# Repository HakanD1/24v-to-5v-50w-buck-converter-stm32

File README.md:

# STM32 Digitally Controlled 24V to 5V (50W) Buck Converter

A high-performance, fully custom **closed-loop digitally controlled buck converter** capable of stepping down a 24V DC input to a highly stable 5V DC output, providing up to 10A (50W) of continuous power. 

This project integrates custom PCB hardware, STM32 embedded software, mathematical control algorithms, and a Nextion HMI (Human-Machine Interface) into a single, cohesive industrial-grade prototype.
> ⚠️ **Project Status:** Rather than turning this into a physical product, I built it as an R&D exercise to combine the full design, simulation, and firmware development process into a single project and put my theoretical background into practice. As a result, the PCB, schematic, and firmware files in this repo have not been manufactured — they've only been verified through design and simulation.

## 🌟 Key Features

*   **Robust Power Delivery:** 24V to 5V step-down conversion with up to 10A current capacity.
*   **Digital PI Control:** Real-time Proportional-Integral (PI) control loop running on an STM32 microcontroller to dynamically adjust the 120 kHz PWM duty cycle for perfect voltage/current regulation.
*   **Precision Measurement:** Hall-effect current sensing (ACS712) and voltage divider networks, both buffered by MCP6001 Op-Amps for noise-immune ADC readings via DMA.
*   **Advanced Gate Driving:** FAN73711 high-speed gate driver implemented to efficiently switch the N-Channel power MOSFET with minimal switching losses.
*   **Multi-Stage Auxiliary Power:** Dual XL4015 buck stages (24V→12V, 12V→5V) and an AMS1117-3.3V LDO to safely isolate and power the logic and driver circuits.
*   **Comprehensive Protection:** Input fuse, varistor for overvoltage spikes, inrush current-limiting thermistor, and a software-controlled mechanical relay for emergency cutoff.
*   **Interactive UI:** Nextion display integration via USART for real-time monitoring (V, I, P) and on-the-fly PI tuning, calibration, and mode switching.

## 🛠️ Hardware Architecture

The custom dual-layer PCB is designed with best practices in mind, separating noisy power switching nodes from sensitive analog measuring circuits.

*   **Power Stage:** Features a 33µH power inductor and low-ESR capacitors optimized through MATLAB/Simulink and LTspice simulations to minimize output ripple.
*   **Protection Layer:** Hardware-level protection blocks ensuring safe start-up and transient spike absorption.
*   **Connectivity:** Features industry-standard ports including USB Type-C (for communication/future updates), 4-pin SWD (for flashing/debugging), and a 4-pin USART header for the HMI.

## 💻 Software & Control Strategy

Developed using **STM32CubeIDE** and the HAL library, the software architecture operates in a non-blocking, interrupt-driven manner:

1.  **ADC via DMA:** Voltage and current analog signals are continuously sampled in the background.
2.  **Calibration Layer:** Raw ADC data is scaled using dynamically adjustable calibration multipliers (`V_Cal`, `I_Cal`) and offsets to compensate for real-world component tolerances.
3.  **PI Algorithm:** Compares the measured value against the user-defined reference. The accumulated error (Integral) and current error (Proportional) dynamically update the timer's compare register to adjust the 120 kHz PWM duty cycle.
4.  **UART Parser:** A custom interrupt-driven parser processes commands from the Nextion screen (e.g., `KPV:2.50`, `SETV:5.00`) to tune the system on the fly.

## 📂 Repository Structure

*   `/bom` - Bill of Materials (BOM) files.
*   `/cubemx` - STM32CubeIDE project workspace and C/C++ source code.
*   `/gerber` - PCB manufacturing and Gerber files.
*   `/Nextion` - Nextion HMI display interface and GUI files.
*   `/schematic_pcb_3d` & `/STEP file` - 3D models and CAD files of the PCB.
*   `buck converter V6.*` - KiCad schematic and PCB design files.
*   `Buck_converter_24Vto5V.asc` - LTspice simulation model.
*   `buck_converter_24Vto5V.slx` - MATLAB/Simulink model.
*   `REPORT.pdf` - Comprehensive project documentation and theoretical calculations (in Turkish).

## 🚀 Getting Started

1.  Clone this repository: `git clone https://github.com/HakanD1/24v-to-5v-50w-buck-converter-stm32`
2.  Open the `/cubemx` project folder in **STM32CubeIDE**.
3.  Compile and flash the firmware onto the STM32F103C8T6 via the SWD interface.
4.  Load the `.tft` file (located in the `/Nextion` folder) onto your Nextion display.
5.  Supply 24V to the main input terminal, and monitor the live parameters on the Nextion screen.

## 📄 License

This project is licensed under the MIT License - see the [LICENSE](LICENSE) file for details.

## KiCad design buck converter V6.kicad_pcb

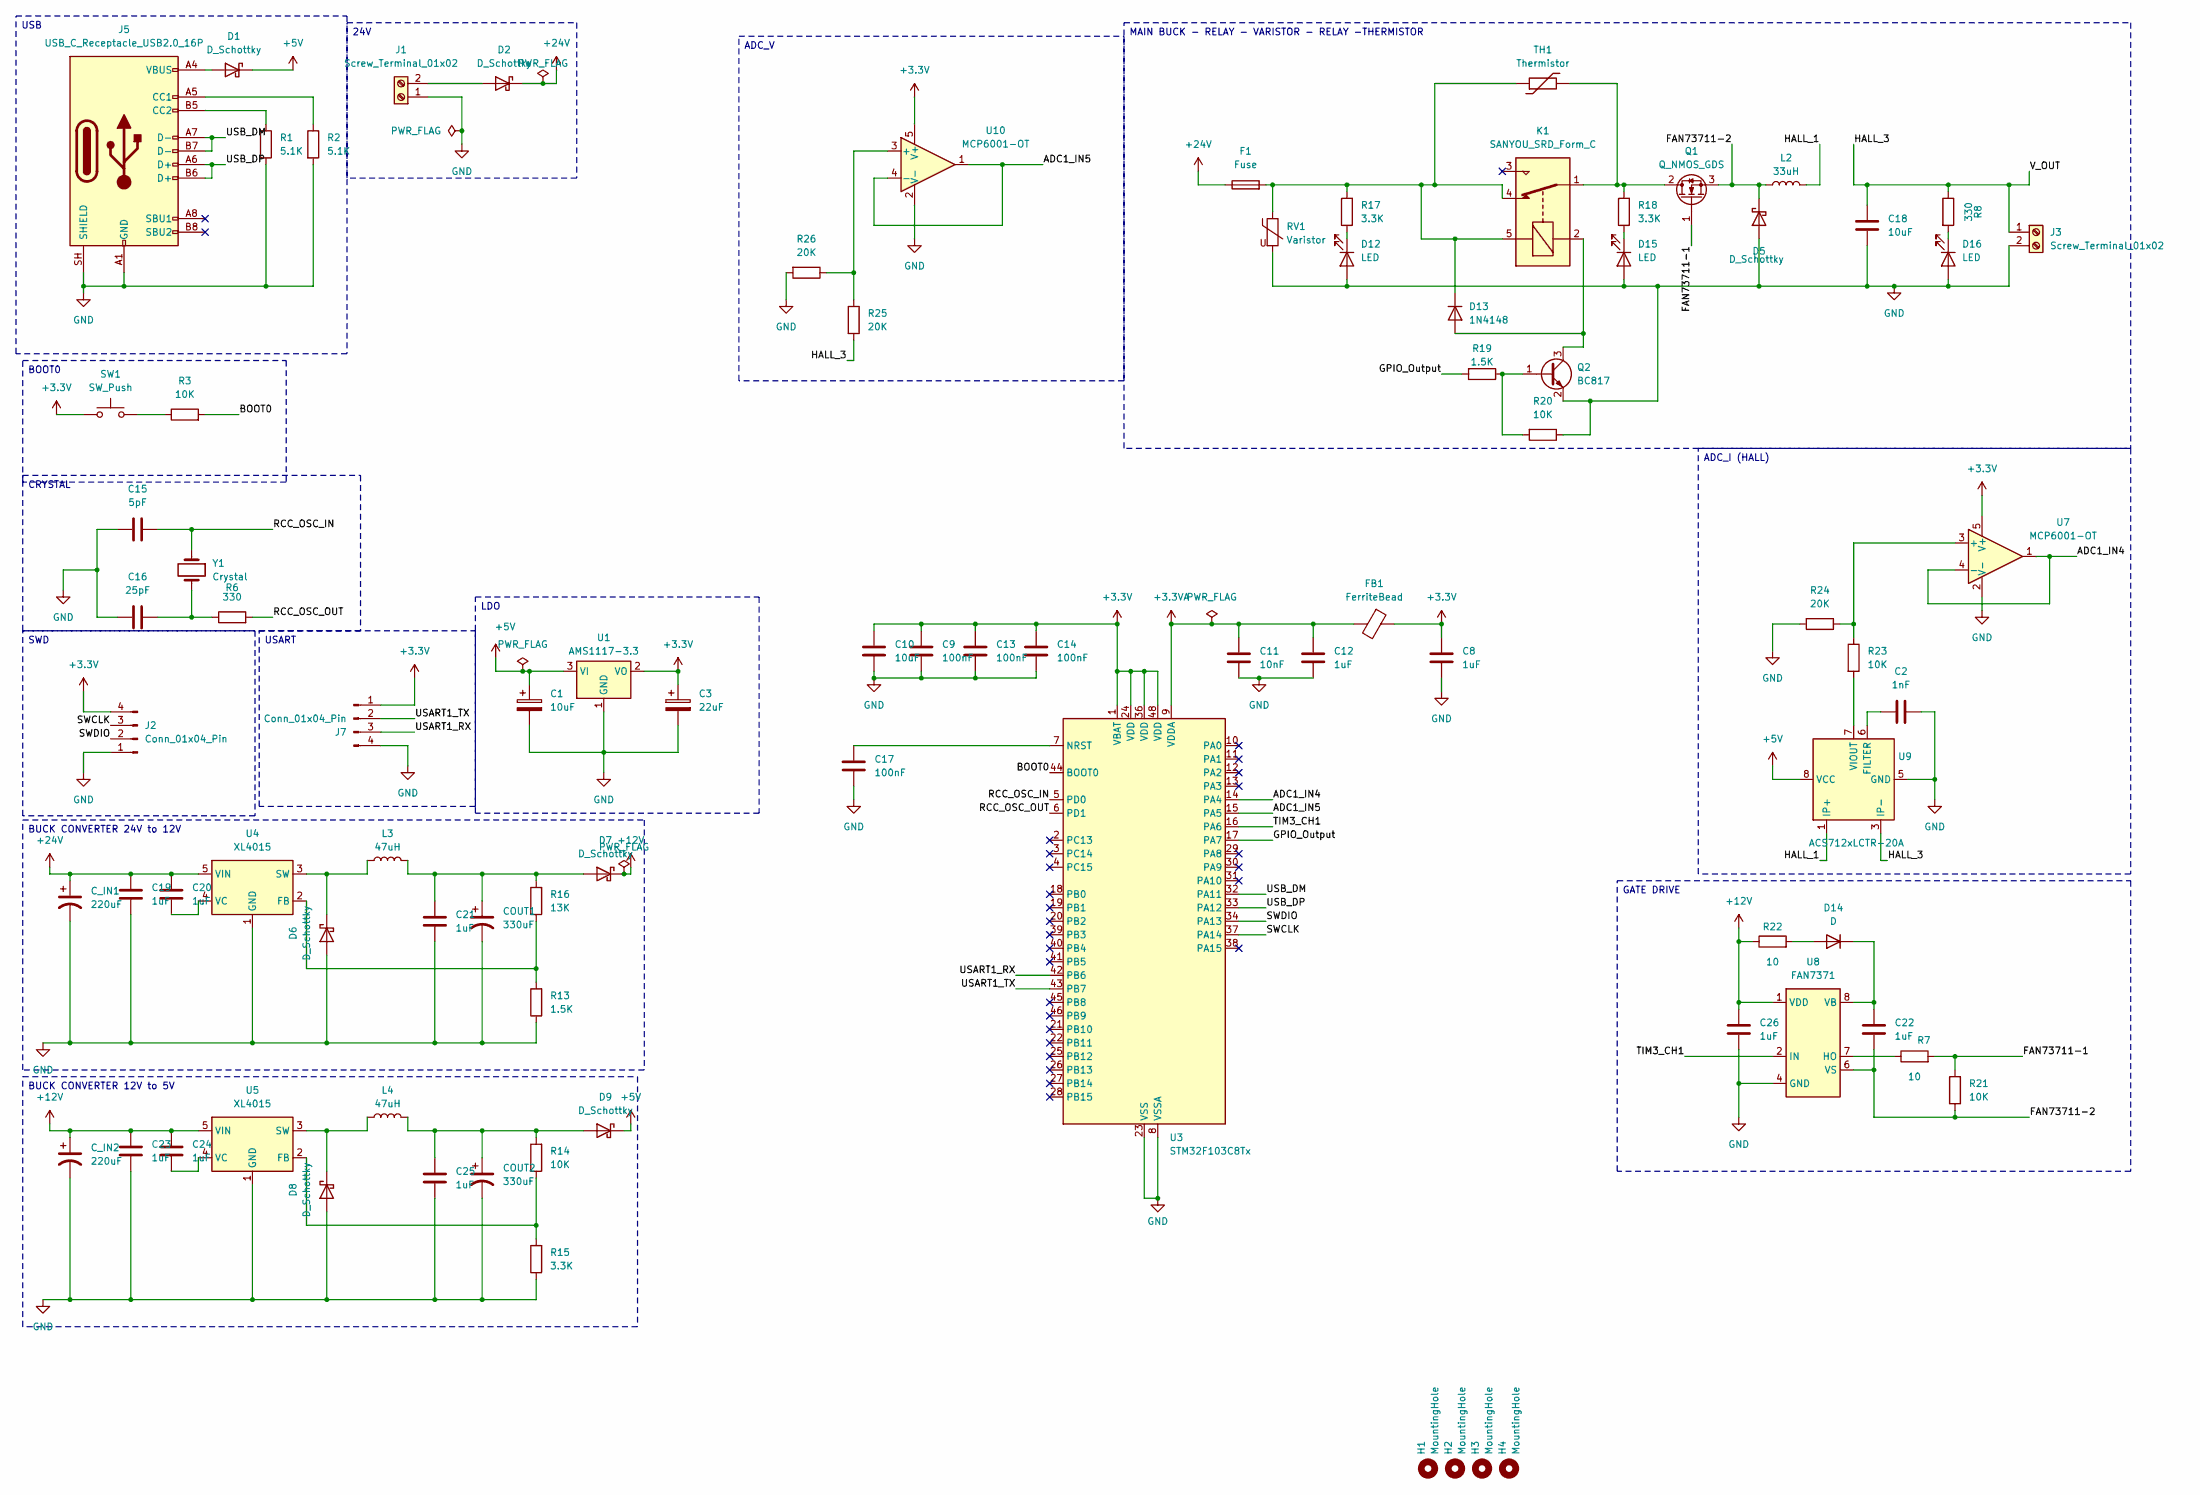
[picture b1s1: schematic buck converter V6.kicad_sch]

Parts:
C1: 10uF; LED_1206_3216Metric_Pad1.42x1.75mm_HandSolder; MPN CA45A010K476TA
C2: 1nF; C_0805_2012Metric_Pad1.18x1.45mm_HandSolder; MPN C0805C102K5RECAUTO
C3: 22uF; LED_1206_3216Metric_Pad1.42x1.75mm_HandSolder; MPN CA45A010K476TA
C8, C12, C19, C20, C21, C22, C23, C24, C25, C26: 1uF; C_0805_2012Metric_Pad1.18x1.45mm_HandSolder; MPN 0805B105K100CC
C9, C13, C14, C17: 100nF; C_0805_2012Metric_Pad1.18x1.45mm_HandSolder; MPN 0805B104K201DC
C10, C18: 10uF; C_0805_2012Metric_Pad1.18x1.45mm_HandSolder; MPN 0805W106K6R3CC
C11: 10nF; C_0805_2012Metric_Pad1.18x1.45mm_HandSolder; MPN 0805B103K251DC
C15: 5pF; C_0805_2012Metric_Pad1.18x1.45mm_HandSolder; MPN 0805N5R0C500AD
C16: 25pF; C_0805_2012Metric_Pad1.18x1.45mm_HandSolder; MPN CC0805JRNPO9BN250
COUT1, COUT2: 330uF; CP_Elec_5x5.8; MPN EL1C471MP51011S
C_IN1, C_IN2: 220uF; CP_Elec_5x5.8; MPN SL157M025HECRR
D1, D2, D5, D7, D9: D_Schottky; D_SMA_Handsoldering; MPN SS54
D6, D8: D_Schottky; D_SOD-123; MPN SD103AW
D12, D15, D16: LED; LED_0805_2012Metric_Pad1.15x1.40mm_HandSolder; MPN LTST-C170KRKT
D13: 1N4148; D_DO-35_SOD27_P7.62mm_Horizontal; MPN 1N4148
D14: D; D_SOD-123F; MPN RS1MWF-7
F1: Fuse; Fuse_0805_2012Metric_Pad1.15x1.40mm_HandSolder; MPN MFU0805FF05000P100
FB1: FerriteBead; L_0603_1608Metric_Pad1.05x0.95mm_HandSolder; MPN MPZ1608S121ATDH5
H1, H2, H3, H4: MountingHole; MountingHole_2.2mm_M2
J1, J3: Screw_Terminal_01x02; TerminalBlock_Phoenix_MKDS-1-2-3.81_1x02_P3.81mm_Horizontal; MPN JL127-50802G01
J2: Conn_01x04_Pin; PinHeader_1x04_P2.54mm_Vertical; MPN D01-9970442
J5: USB_C_Receptacle_USB2.0_16P; USB_C_Receptacle_GCT_USB4105-xx-A_16P_TopMnt_Horizontal; MPN USB4105-GF-A
J7: Conn_01x04_Pin; JST_XH_B4B-XH-A_1x04_P2.50mm_Vertical; MPN B4B-XH-A
K1: SANYOU_SRD_Form_C; Relay_SPDT_SANYOU_SRD_Series_Form_C; MPN SRD-24VDC-SL-C
L2: 33uH; L_Sunlord_MWSA1205S-330; MPN 125CDMCCDS-330MC
L3, L4: 47uH; L_Bourns_SRR1210A; MPN SRR1210-470M
Q1: Q_NMOS_GDS; TO-220-3_Vertical; MPN AUIRL3705N
Q2: BC817; SOT-23; MPN BC817
R1, R2: 5.1K; R_0805_2012Metric_Pad1.20x1.40mm_HandSolder; MPN RM10J512CT
R3, R14, R20, R21, R23: 10K; R_0805_2012Metric_Pad1.20x1.40mm_HandSolder; MPN RM10J103CT
R6, R8: 330; R_0805_2012Metric_Pad1.20x1.40mm_HandSolder; MPN RM10J331CT
R7, R22: 10; R_0805_2012Metric_Pad1.20x1.40mm_HandSolder; MPN ERJ-6ENF10R0V
R13, R19: 1.5K; R_0805_2012Metric_Pad1.20x1.40mm_HandSolder; MPN RM10F1501CT
R15, R17, R18: 3.3K; R_0805_2012Metric_Pad1.20x1.40mm_HandSolder; MPN RM10J332CT
R16: 13K; R_0805_2012Metric_Pad1.20x1.40mm_HandSolder; MPN RM10J133CT
R24, R25, R26: 20K; R_0805_2012Metric_Pad1.20x1.40mm_HandSolder; MPN ERJ-6ENF2002V
RV1: Varistor; RV_Disc_D12mm_W4.6mm_P7.5mm; MPN 10D390K
SW1: SW_Push; SW_PUSH_6mm; MPN ZX-QC66-8.5TP
TH1: Thermistor; RV_Disc_D12mm_W4.4mm_P7.5mm; MPN SURGING 10D-11
U1: AMS1117-3.3; SOT-223-3_TabPin2; MPN AMS1117-3.3
U3: STM32F103C8Tx; LQFP-48_7x7mm_P0.5mm; MPN STM32F103C8T6
U4, U5: XL4015; TO-263-5_TabPin3; MPN XL4015E1
U7, U10: MCP6001-OT; SOT-23-5_HandSoldering; MPN MCP6001T-I/OT
U8: FAN7371; SOIC-8_3.9x4.9mm_P1.27mm; MPN FAN73711MX
U9: ACS712xLCTR-20A; SOIC-8_3.9x4.9mm_P1.27mm; MPN ACS712ELCTR-20A-T
Y1: Crystal; Crystal_SMD_5032-2Pin_5.0x3.2mm; MPN 0153G2-8.000F22DTNLK

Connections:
+3.3V: C3.1, C8.1, C9.1, C10.1, C13.1, C14.1, FB1.1, J2.4, J7.1, SW1.1, U1.2 (VO), U3.1 (VBAT), U3.24 (VDD), U3.36 (VDD), U3.48 (VDD), U7.5 (V+), U10.5 (V+)
+3.3VA: C11.1, C12.1, FB1.2, U3.9 (VDDA)
+5V: C1.1, D1.1 (K), D9.1 (K), U1.3 (VI), U9.8 (VCC)
+12V: C23.1, C24.1, C26.1, C_IN2.1, D7.1 (K), R22.1, U5.5 (VIN), U8.1 (VDD)
+24V: C19.1, C20.1, C_IN1.1, D2.1 (K), F1.1, U4.5 (VIN)
/ADC1_IN4: U3.14 (PA4), U7.1, U7.4 (-)
/ADC1_IN5: U3.15 (PA5), U10.1, U10.4 (-)
/BOOT0: R3.2, U3.44 (BOOT0)
/FAN73711-1: Q1.1 (G), R7.2, R21.2
/FAN73711-2: C22.2, D5.1 (K), L2.1, Q1.3 (S), R21.1, U8.6 (VS)
/GPIO_Output: R19.2, U3.17 (PA7)
/HALL_1: L2.2, U9.1 (IP+), U9.2 (IP+)
/HALL_3: C18.1, J3.1, R8.1, R25.2, U9.3 (IP-), U9.4 (IP-)
/RCC_OSC_IN: C15.2, U3.5 (PD0), Y1.1
/RCC_OSC_OUT: R6.2, U3.6 (PD1)
/SWCLK: J2.3, U3.37 (PA14)
/SWDIO: J2.2, U3.34 (PA13)
/TIM3_CH1: U3.16 (PA6), U8.2 (IN)
/USART1_RX: J7.3, U3.42 (PB6)
/USART1_TX: J7.2, U3.43 (PB7)
/USB_DM: J5.A7 (D-), J5.B7 (D-), U3.32 (PA11)
/USB_DP: J5.A6 (D+), J5.B6 (D+), U3.33 (PA12)
GND: C1.2, C2.2, C3.2, C8.2, C9.2, C10.2, C11.2, C12.2, C13.2, C14.2, C15.1, C16.1, C17.2, C18.2, C19.2, C21.2, C23.2, C25.2, C26.2, COUT1.2, COUT2.2, C_IN1.2, C_IN2.2, D5.2 (A), D6.2 (A), D8.2 (A), D12.2 (A), D15.2 (A), D16.2 (A), J1.1, J2.1, J3.2, J5.A1 (GND), J5.A12 (GND), J5.B1 (GND), J5.B12 (GND), J5.SH (SHIELD), J7.4, Q2.2 (E), R1.2, R2.2, R13.1, R15.1, R20.1, R24.2, R26.2, RV1.2, U1.1 (GND), U3.8 (VSSA), U3.23 (VSS), U3.35 (VSS), U3.47 (VSS), U4.1 (GND), U5.1 (GND), U7.2 (V-), U8.4 (GND), U9.5 (GND), U10.2 (V-)
unnamed: C16.2, R6.1, Y1.2
unnamed: D1.2 (A), J5.A4 (VBUS), J5.A9 (VBUS), J5.B4 (VBUS), J5.B9 (VBUS)
unnamed: D2.2 (A), J1.2
unnamed: D6.1 (K), L3.1, U4.3 (SW)
unnamed: C21.1, COUT1.1, D7.2 (A), L3.2, R16.2
unnamed: D8.1 (K), L4.1, U5.3 (SW)
unnamed: C25.1, COUT2.1, D9.2 (A), L4.2, R14.2
unnamed: D12.1 (K), R17.1
unnamed: D13.2 (A), K1.2, Q2.3 (C)
unnamed: D13.1 (K), F1.2, K1.4, K1.5, R17.2, RV1.1, TH1.1
unnamed: D14.2 (A), R22.2
unnamed: C22.1, D14.1 (K), U8.8 (VB)
unnamed: D15.1 (K), R18.1
unnamed: D16.1 (K), R8.2
unnamed: J5.A5 (CC1), R2.1
unnamed: J5.B5 (CC2), R1.1
unnamed: K1.1, Q1.2 (D), R18.2, TH1.2
unnamed: Q2.1 (B), R19.1, R20.2
unnamed: R3.1, SW1.2
unnamed: C17.1, U3.7 (NRST)
unnamed: R13.2, R16.1, U4.2 (FB)
unnamed: C20.2, U4.4 (VC)
unnamed: R14.1, R15.2, U5.2 (FB)
unnamed: C24.2, U5.4 (VC)
unnamed: R23.1, R24.1, U7.3 (+)
unnamed: R7.1, U8.7 (HO)
unnamed: C2.1, U9.6 (FILTER)
unnamed: R23.2, U9.7 (VIOUT)
unnamed: R25.1, R26.1, U10.3 (+)

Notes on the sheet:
ADC_V
USB
LDO
BOOT0
SWD
GATE DRIVE
24V
BUCK CONVERTER 24V to 12V
BUCK CONVERTER 12V to 5V
USART
MAIN BUCK - RELAY - VARISTOR - RELAY -THERMISTOR
CRYSTAL
ADC_I (HALL)

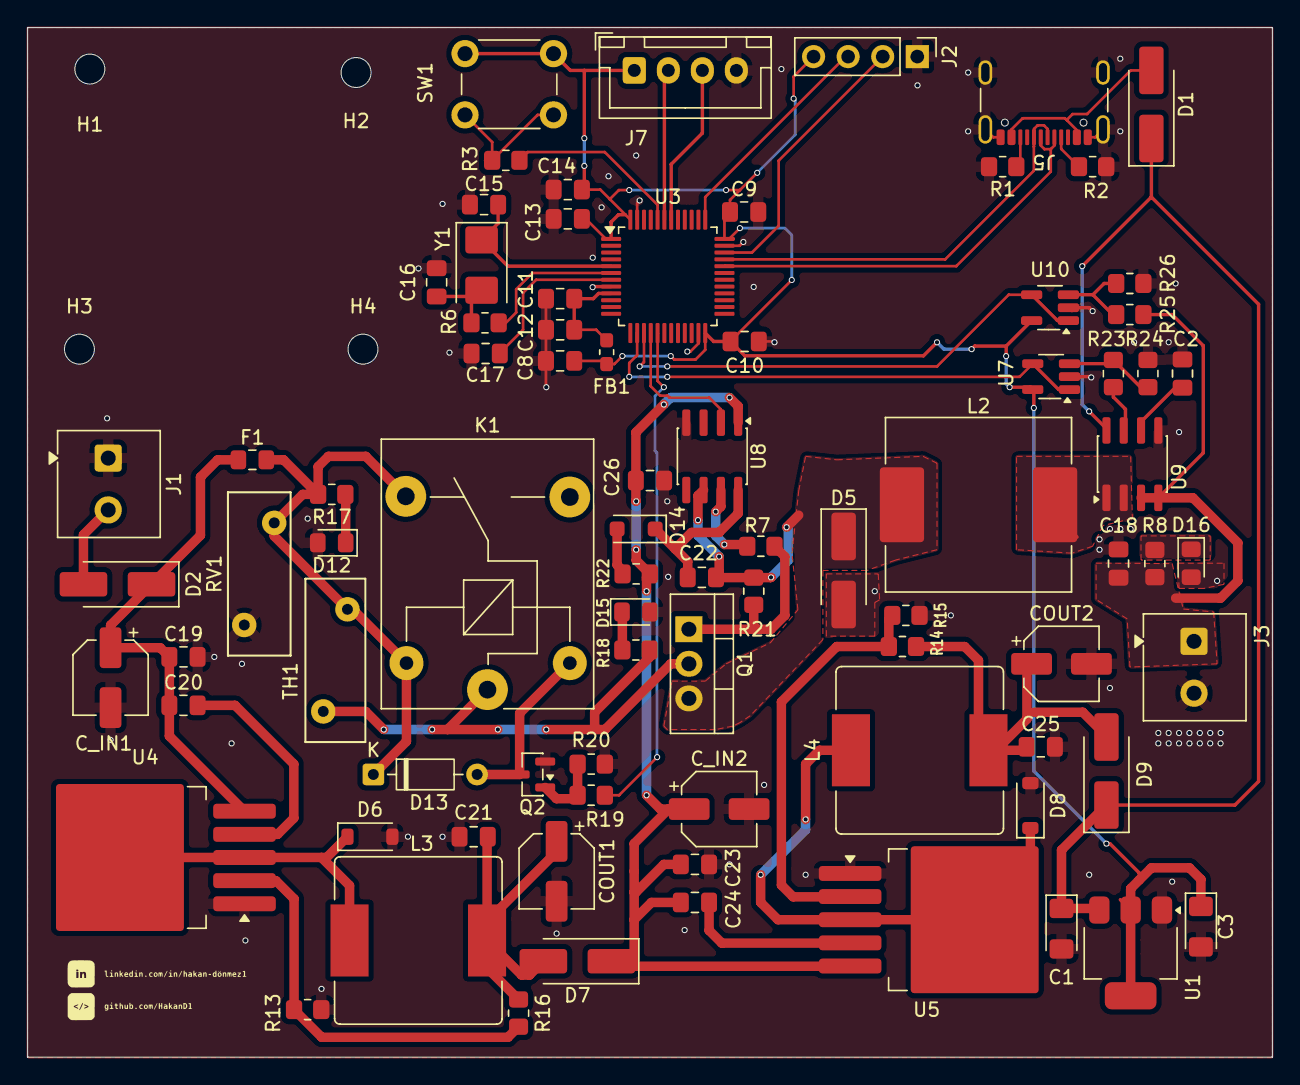
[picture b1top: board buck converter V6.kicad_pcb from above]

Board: 2 copper layers, 91.4 x 75.6 mm, 88 parts (0 on the bottom side), 52 nets.

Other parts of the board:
.: LOGO; logo1

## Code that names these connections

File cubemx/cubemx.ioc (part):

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Mcu.Name=STM32F103C(8-B)Tx
Mcu.Package=LQFP48
Mcu.UserName=STM32F103C8Tx
PA11.Mode=Device
PA11.Signal=USB_DM
PA12.Mode=Device
PA12.Signal=USB_DP
PA13.Mode=Serial_Wire
PA13.Signal=SYS_JTMS-SWDIO
PA14.Mode=Serial_Wire
PA14.Signal=SYS_JTCK-SWCLK
PA15.Mode=NSS_Signal_Hard_Output
PA15.Signal=SPI1_NSS
PA4.Signal=ADCx_IN4
PA5.Signal=ADCx_IN5
PA6.Signal=S_TIM3_CH1
PA7.Signal=GPIO_Output
PB10.Mode=I2C
PB10.Signal=I2C2_SCL
PB11.Mode=I2C
PB11.Signal=I2C2_SDA
PB3.Mode=Full_Duplex_Master
PB3.Signal=SPI1_SCK
PB4.Mode=Full_Duplex_Master
PB4.Signal=SPI1_MISO
PB5.Mode=Full_Duplex_Master
PB5.Signal=SPI1_MOSI
PB6.Mode=Asynchronous
PB6.Signal=USART1_TX
PB7.Mode=Asynchronous
PB7.Signal=USART1_RX
PD0-OSC_IN.Mode=HSE-External-Oscillator
PD0-OSC_IN.Signal=RCC_OSC_IN
PD1-OSC_OUT.Mode=HSE-External-Oscillator
PD1-OSC_OUT.Signal=RCC_OSC_OUT
RCC.SYSCLKFreq_VALUE=48000000
RCC.SYSCLKSource=RCC_SYSCLKSOURCE_PLLCLK
board=custom

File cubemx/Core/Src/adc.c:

/* USER CODE BEGIN Header */
/**
  ******************************************************************************
  * @file    adc.c
  * @brief   This file provides code for the configuration
  *          of the ADC instances.
  ******************************************************************************
  * @attention
  *
  * Copyright (c) 2026 STMicroelectronics.
  * All rights reserved.
  *
  * This software is licensed under terms that can be found in the LICENSE file
  * in the root directory of this software component.
  * If no LICENSE file comes with this software, it is provided AS-IS.
  *
  ******************************************************************************
  */
/* USER CODE END Header */
/* Includes ------------------------------------------------------------------*/
#include "adc.h"

/* USER CODE BEGIN 0 */

/* USER CODE END 0 */

ADC_HandleTypeDef hadc1;
DMA_HandleTypeDef hdma_adc1;

/* ADC1 init function */
void MX_ADC1_Init(void)
{

  /* USER CODE BEGIN ADC1_Init 0 */

  /* USER CODE END ADC1_Init 0 */

  ADC_ChannelConfTypeDef sConfig = {0};

  /* USER CODE BEGIN ADC1_Init 1 */

  /* USER CODE END ADC1_Init 1 */

  /** Common config
  */
  hadc1.Instance = ADC1;
  hadc1.Init.ScanConvMode = ADC_SCAN_ENABLE;
  hadc1.Init.ContinuousConvMode = ENABLE;
  hadc1.Init.DiscontinuousConvMode = DISABLE;
  hadc1.Init.ExternalTrigConv = ADC_SOFTWARE_START;
  hadc1.Init.DataAlign = ADC_DATAALIGN_RIGHT;
  hadc1.Init.NbrOfConversion = 2;
  if (HAL_ADC_Init(&hadc1) != HAL_OK)
  {
    Error_Handler();
  }

  /** Configure Regular Channel
  */
  sConfig.Channel = ADC_CHANNEL_4;
  sConfig.Rank = ADC_REGULAR_RANK_1;
  sConfig.SamplingTime = ADC_SAMPLETIME_1CYCLE_5;
  if (HAL_ADC_ConfigChannel(&hadc1, &sConfig) != HAL_OK)
  {
    Error_Handler();
  }

  /** Configure Regular Channel
  */
  sConfig.Channel = ADC_CHANNEL_5;
  sConfig.Rank = ADC_REGULAR_RANK_2;
  if (HAL_ADC_ConfigChannel(&hadc1, &sConfig) != HAL_OK)
  {
    Error_Handler();
  }
  /* USER CODE BEGIN ADC1_Init 2 */

  /* USER CODE END ADC1_Init 2 */

}

void HAL_ADC_MspInit(ADC_HandleTypeDef* adcHandle)
{

  GPIO_InitTypeDef GPIO_InitStruct = {0};
  if(adcHandle->Instance==ADC1)
  {
  /* USER CODE BEGIN ADC1_MspInit 0 */

  /* USER CODE END ADC1_MspInit 0 */
    /* ADC1 clock enable */
    __HAL_RCC_ADC1_CLK_ENABLE();

    __HAL_RCC_GPIOA_CLK_ENABLE();
    /**ADC1 GPIO Configuration
    PA4     ------> ADC1_IN4
    PA5     ------> ADC1_IN5
    */
    GPIO_InitStruct.Pin = GPIO_PIN_4|GPIO_PIN_5;
    GPIO_InitStruct.Mode = GPIO_MODE_ANALOG;
    HAL_GPIO_Init(GPIOA, &GPIO_InitStruct);

    /* ADC1 DMA Init */
    /* ADC1 Init */
    hdma_adc1.Instance = DMA1_Channel1;
    hdma_adc1.Init.Direction = DMA_PERIPH_TO_MEMORY;
    hdma_adc1.Init.PeriphInc = DMA_PINC_DISABLE;
    hdma_adc1.Init.MemInc = DMA_MINC_ENABLE;
    hdma_adc1.Init.PeriphDataAlignment = DMA_PDATAALIGN_HALFWORD;
    hdma_adc1.Init.MemDataAlignment = DMA_MDATAALIGN_HALFWORD;
    hdma_adc1.Init.Mode = DMA_CIRCULAR;
    hdma_adc1.Init.Priority = DMA_PRIORITY_LOW;
    if (HAL_DMA_Init(&hdma_adc1) != HAL_OK)
    {
      Error_Handler();
    }

    __HAL_LINKDMA(adcHandle,DMA_Handle,hdma_adc1);

  /* USER CODE BEGIN ADC1_MspInit 1 */

  /* USER CODE END ADC1_MspInit 1 */
  }
}

void HAL_ADC_MspDeInit(ADC_HandleTypeDef* adcHandle)
{

  if(adcHandle->Instance==ADC1)
  {
  /* USER CODE BEGIN ADC1_MspDeInit 0 */

  /* USER CODE END ADC1_MspDeInit 0 */
    /* Peripheral clock disable */
    __HAL_RCC_ADC1_CLK_DISABLE();

    /**ADC1 GPIO Configuration
    PA4     ------> ADC1_IN4
    PA5     ------> ADC1_IN5
    */
    HAL_GPIO_DeInit(GPIOA, GPIO_PIN_4|GPIO_PIN_5);

    /* ADC1 DMA DeInit */
    HAL_DMA_DeInit(adcHandle->DMA_Handle);
  /* USER CODE BEGIN ADC1_MspDeInit 1 */

  /* USER CODE END ADC1_MspDeInit 1 */
  }
}

/* USER CODE BEGIN 1 */

/* USER CODE END 1 */

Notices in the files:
README.md:
License: MIT
